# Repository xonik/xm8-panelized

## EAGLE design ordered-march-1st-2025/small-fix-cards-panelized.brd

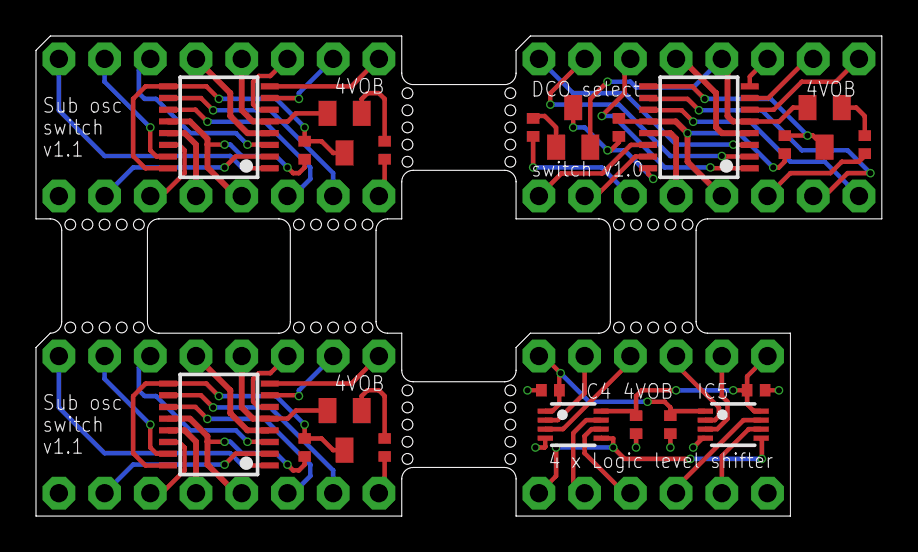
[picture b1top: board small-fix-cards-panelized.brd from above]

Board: 2 copper layers, 47.0 x 26.7 mm, 29 parts (0 on the bottom side), 66 nets.

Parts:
C1, C2, C3, C4: 1uF; C0402-J
IC1, IC2, IC3: DG412-JT; TSSOP16J
IC4, IC5: SN74LVC2T45; VSSOP8J
R1, R2, R5, R6: 10k; R0402
R3, R4, R7, R8: 470R; R0402
T1, T2, T3, T4: 2n3904; SOT23-BEC
X1, X2, X3, X4, X5, X6: ROUND-IC-PIN; MA08N-1J
X7, X8: MA06-1JN; MA06N-1J

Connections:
1_A_SUB_WAVE: IC2.1, X1.1
1_A_SUB_WAVE1: IC1.1, X3.1
1_OSC_B_OUT: IC3.3, X5.1
2_SSA1A: IC2.15, X1.2
2_SSA1A1: IC1.15, X3.2
2_WAVE_B_OUT: IC3.2, X5.2
3_A_SUB_1: IC2.3, X1.3
3_A_SUB_2: IC1.3, X3.3
3_B_MODE: IC3.1, X5.3
6_A_MODE: IC3.8, X5.6
6_A_SUB_1: IC1.6, X3.6
6_A_SUB_2: IC2.6, X1.6
7_SSQ2A: IC2.7, X1.7
7_SSQ2A1: IC1.7, X3.7
7_WAVE_A_OUT: IC3.7, X5.7
8_A_SUB_WAVE: IC2.8, X1.8
8_A_SUB_WAVE1: IC1.8, X3.8
8_OSC_A_OUT: IC3.6, X5.8
9_A_SUB_WAVE: R2.1, X2.1
9_A_SUB_WAVE1: R1.1, X4.1
9_OSC_A_OUT: IC3.11, X6.1
10_SSA2A: IC2.10, X2.2
10_SSA2A1: IC1.10, X4.2
10_WF_A_OUT: IC3.10, X6.2
11_A_MODE: R6.1, X6.3
11_A_SUB_1: IC1.11, X4.3
11_A_SUB_2: IC2.11, X2.3
11_NOT_A_MODE: IC3.9, R8.1, T4.C
14_A_SUB_1: IC2.14, X2.6
14_A_SUB_2: IC1.14, X4.6
14_B_MODE: R5.1, X6.6
14_NOT_B_MODE: IC3.16, R7.1, T3.C
15_SSQ1A: IC2.2, X2.7
15_SSQ1A1: IC1.2, X4.7
15_WF_B_OUT: IC3.15, X6.7
16_OSC_B_OUT: IC3.14, X6.8
+3V3: C1.1, C3.1, IC4.1, IC5.1, X7.1
+5V: C2.1, C4.1, IC4.8, IC5.8, X7.6
A3: IC4.2, X7.2
A4: IC4.3, X7.3
A5: IC5.2, X7.4
A6: IC5.3, X7.5
B1: IC4.7, X8.5
B2: IC4.6, X8.4
B3: IC5.7, X8.3
B4: IC5.6, X8.2
DIR: IC4.5, IC5.5, X8.6
GND: IC2.5, T2.E, X1.5
GND1: IC1.5, T1.E, X3.5
GND2: IC3.5, T3.E, T4.E, X5.5
GND3: C1.2, C2.2, C3.2, C4.2, IC4.4, IC5.4, X8.1
unnamed: R1.2, T1.B
unnamed: R2.2, T2.B
unnamed: R5.2, T3.B
unnamed: R6.2, T4.B
NOT_A_SUB_WAVE: IC2.9, IC2.16, R4.1, T2.C
NOT_A_SUB_WAVE1: IC1.9, IC1.16, R3.1, T1.C
V+: IC2.13, X2.5
V+1: IC1.13, X4.5
V+2: IC3.13, X6.5
V-: IC2.4, X1.4
V-1: IC1.4, X3.4
V-2: IC3.4, X5.4
V_L: IC2.12, R4.2, X2.4
V_L1: IC1.12, R3.2, X4.4
V_L2: IC3.12, R7.2, R8.2, X6.4

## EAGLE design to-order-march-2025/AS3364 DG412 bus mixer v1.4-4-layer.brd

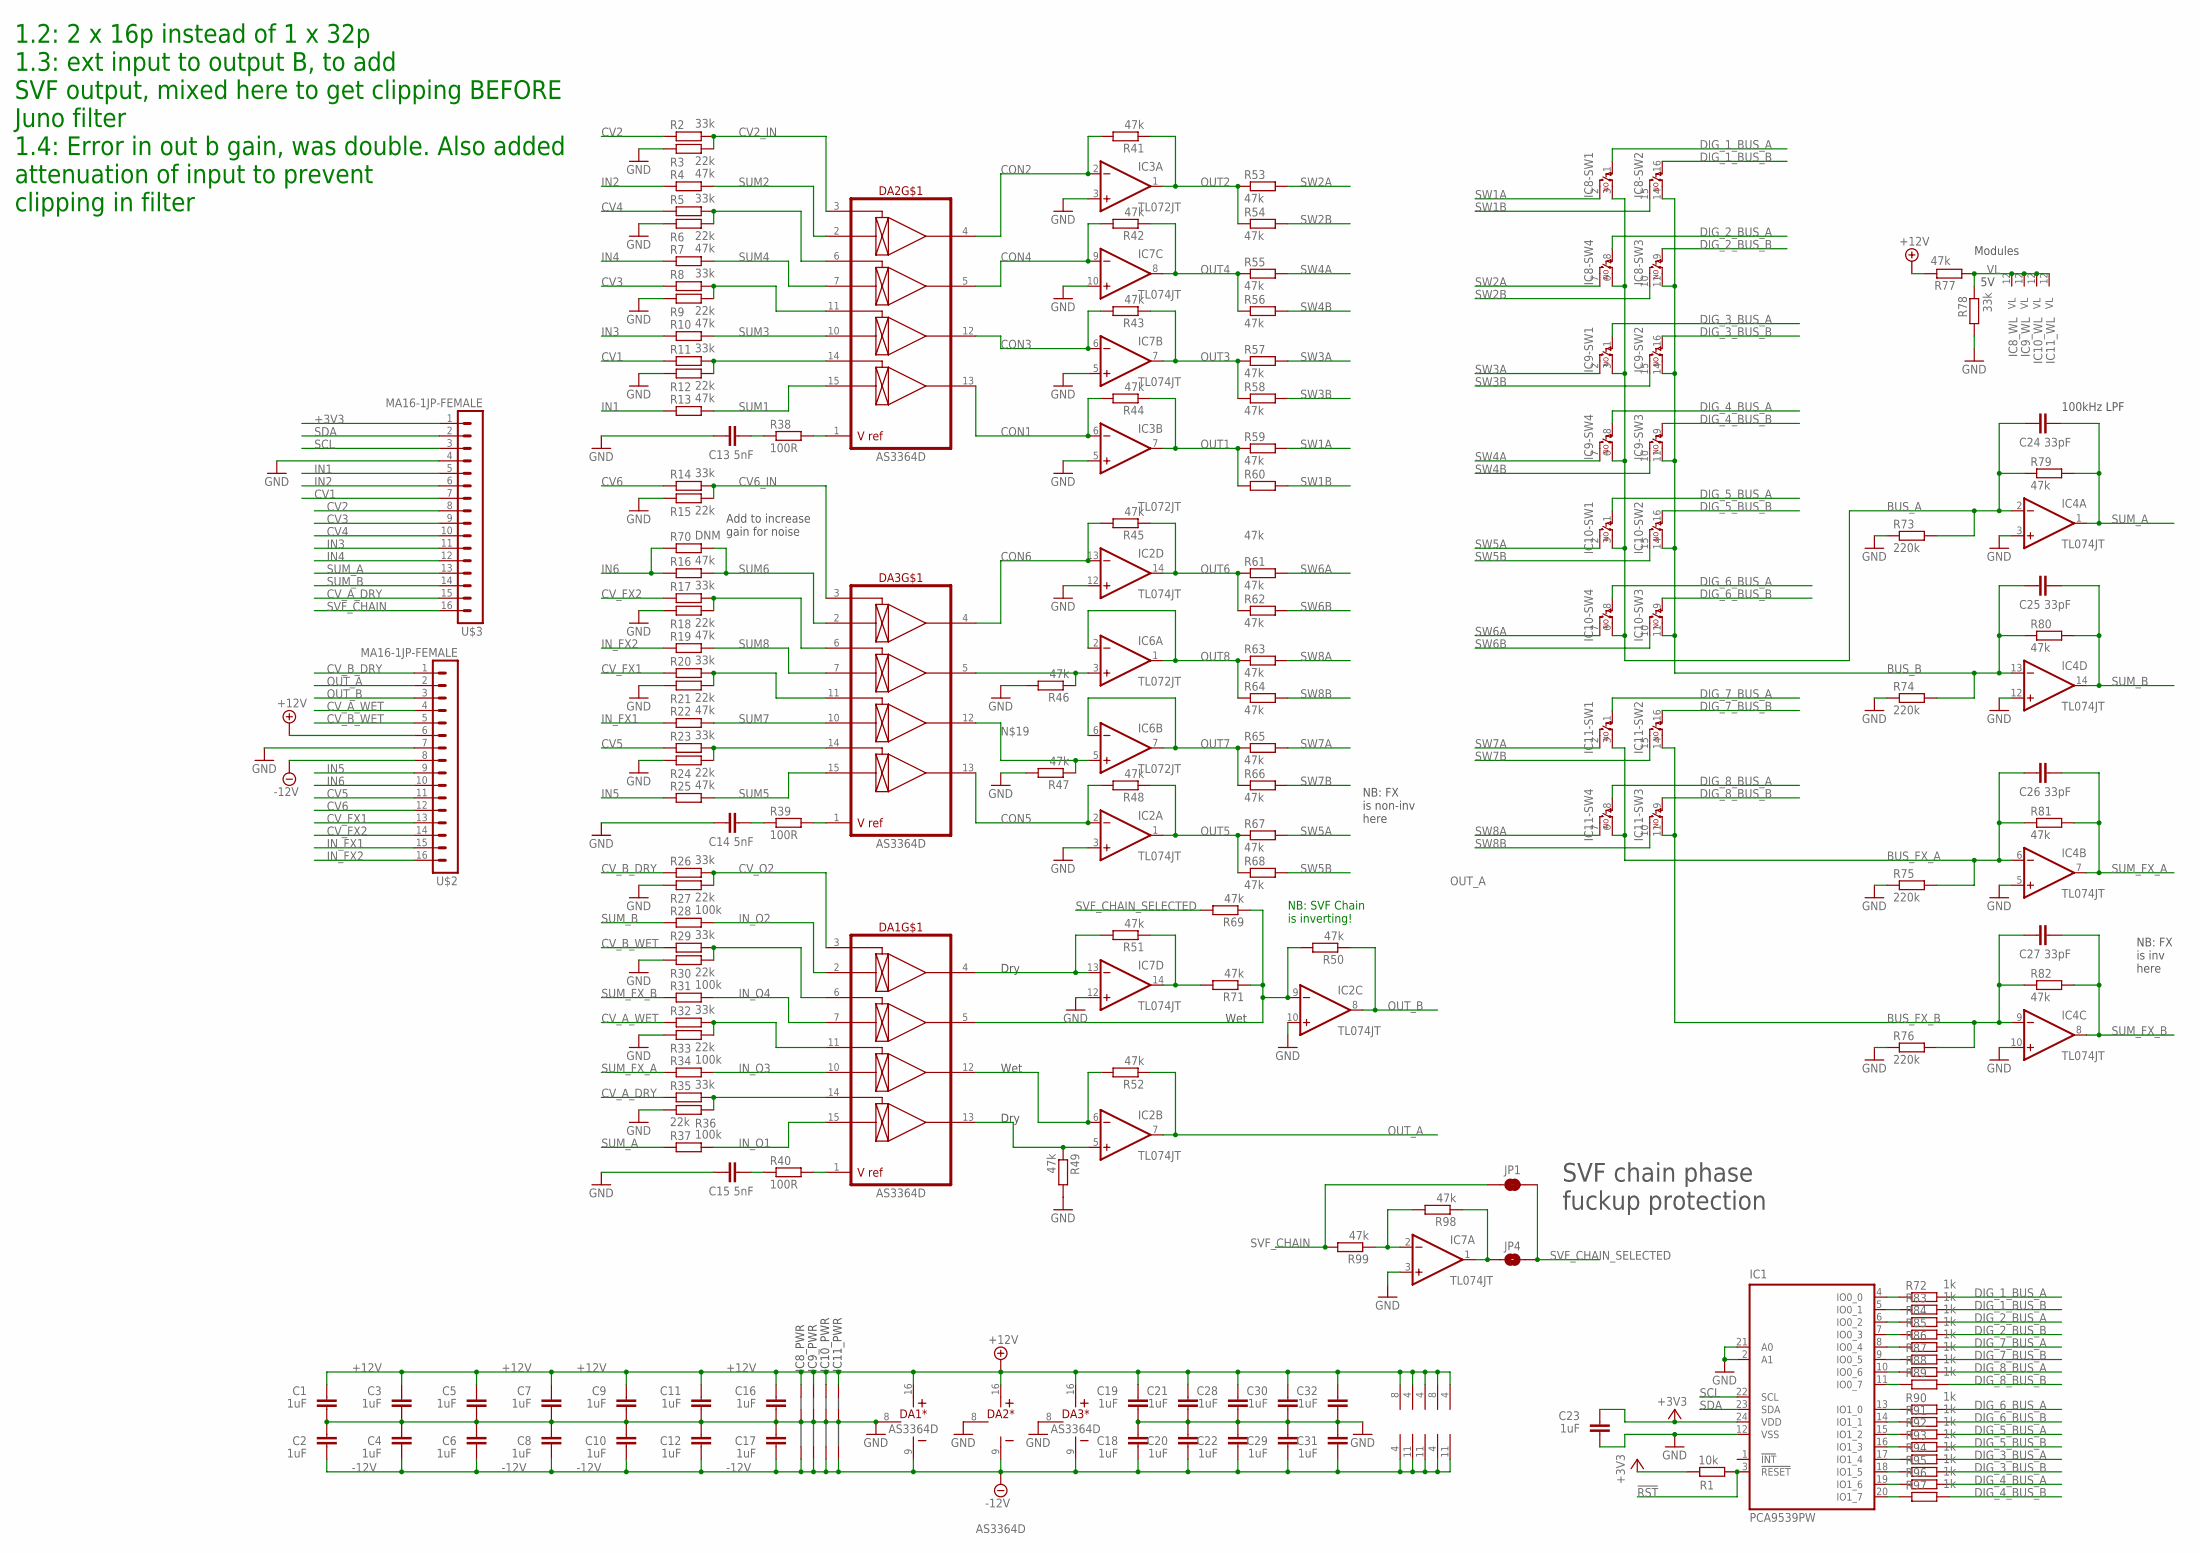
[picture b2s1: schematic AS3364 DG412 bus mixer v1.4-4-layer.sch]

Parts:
C1, C2, C3, C4, C5, C6, C7, C8, C9, C10, C11, C12, C16, C17, C18, C19, C20, C21, C22, C23, C28, C29, C30, C31, C32: 1uF; C0402-J
C13, C14, C15: 5nF; C0402-J
C24, C25, C26, C27: 33pF; C0402-J
DA1, DA2, DA3: AS3364D; DIL16J
IC1: PCA9539PW; TSSOP24J
IC2, IC4, IC7: TL074JT; TSSOP14J
IC3, IC6: TL072JT; TSSOP8J
IC8, IC9, IC10, IC11: DG412-J; DIL16J
JP1: JUMPER-SMT_2_NC_TRACE_SILK-DNM; SMT-JUMPER_2_NC_TRACE_SILK
JP4: JUMPER-SMT_2_NO_SILK-DNM; SMT-JUMPER_2_NO_SILK
R1: 10k; R0402
R2, R5, R8, R11, R14, R17, R20, R23, R26, R29, R32, R35, R78: 33k; R0402
R3, R6, R9, R12, R15, R18, R21, R24, R27, R30, R33, R36: 22k; R0402
R4, R7, R10, R13, R16, R19, R22, R25, R41, R42, R43, R44, R45, R46, R47, R48, R49, R50, R51, R52, R53, R54, R55, R56, R57, R58, R59, R60, R61, R62, R63, R64, R65, R66, R67, R68, R69, R71, R77, R79, R80, R81, R82, R98, R99: 47k; R0402
R28, R31, R34, R37: 100k; R0402
R38, R39, R40: 100R; R0402
R70: DNM; R0805
R72, R83, R84, R85, R86, R87, R88, R89, R90, R91, R92, R93, R94, R95, R96, R97: 1k; R0402
R73, R74, R75, R76: 220k; R0603
U$2, U$3: MA16-1JP-FEMALE; SIP-PIN16-1J

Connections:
!RST: IC1.3 (!RESET), R1.2
+3V3: C23.2, IC1.24 (VDD), R1.1, U$3.1
+12V: C1.2, C3.2, C5.2, C7.2, C9.2, C11.2, C16.2, C19.2, C21.2, C28.2, C30.2, C32.2, DA1.16 (V+), DA2.16 (V+), DA3.16 (V+), IC2.4 (V+), IC3.8 (V+), IC4.4 (V+), IC6.8 (V+), IC7.4 (V+), IC8.13 (+15V), IC9.13 (+15V), IC10.13 (+15V), IC11.13 (+15V), R77.1, U$2.6
-12V: C2.1, C4.1, C6.1, C8.1, C10.1, C12.1, C17.1, C18.1, C20.1, C22.1, C29.1, C31.1, DA1.9 (V-), DA2.9 (V-), DA3.9 (V-), IC2.11 (V-), IC3.4 (V-), IC4.11 (V-), IC6.4 (V-), IC7.11 (V-), IC8.4 (-15V), IC9.4 (-15V), IC10.4 (-15V), IC11.4 (-15V), U$2.8
BUS_A: C24.1, IC4.2 (-IN), IC8.3 (S), IC8.6 (S), IC9.3 (S), IC9.6 (S), IC10.3 (S), IC10.6 (S), R73.2, R79.1
BUS_B: C25.1, IC4.13 (-IN), IC8.11 (S), IC8.14 (S), IC9.11 (S), IC9.14 (S), IC10.11 (S), IC10.14 (S), R74.2, R80.1
BUS_FX_A: C26.1, IC4.6 (-IN), IC11.3 (S), IC11.6 (S), R75.2, R81.1
BUS_FX_B: C27.1, IC4.9 (-IN), IC11.11 (S), IC11.14 (S), R76.2, R82.1
CON1: DA2.13 (OUT4), IC3.6 (-IN), R44.2
CON2: DA2.4 (OUT1), IC3.2 (-IN), R41.2
CON3: DA2.12 (OUT3), IC7.6 (-IN), R43.2
CON4: DA2.5 (OUT2), IC7.9 (-IN), R42.2
CON5: DA3.13 (OUT4), IC2.2 (-IN), R48.2
CON6: DA3.4 (OUT1), IC2.13 (-IN), R45.2
CON_O1: DA1.12 (OUT3), IC2.6 (-IN), R52.2
CV1: R11.1, U$3.7
CV2: R2.1, U$3.8
CV2_IN: DA2.3 (CV1), R2.2, R3.2
CV3: R8.1, U$3.9
CV4: R5.1, U$3.10
CV5: R23.1, U$2.11
CV6: R14.1, U$2.12
CV6_IN: DA3.3 (CV1), R14.2, R15.2
CV_A_DRY: R35.1, U$3.15
CV_A_WET: R32.1, U$2.4
CV_B_DRY: R26.1, U$2.1
CV_B_WET: R29.1, U$2.5
CV_FX1: R20.1, U$2.13
CV_FX2: R17.1, U$2.14
CV_O2: DA1.3 (CV1), R26.2, R27.2
DIG_1_BUS_A: IC8.1 (C), R72.2
DIG_1_BUS_B: IC8.16 (C), R83.2
DIG_2_BUS_A: IC8.8 (C), R84.2
DIG_2_BUS_B: IC8.9 (C), R85.2
DIG_3_BUS_A: IC9.1 (C), R94.2
DIG_3_BUS_B: IC9.16 (C), R95.2
DIG_4_BUS_A: IC9.8 (C), R96.2
DIG_4_BUS_B: IC9.9 (C), R97.2
DIG_5_BUS_A: IC10.1 (C), R92.2
DIG_5_BUS_B: IC10.16 (C), R93.2
DIG_6_BUS_A: IC10.8 (C), R90.2
DIG_6_BUS_B: IC10.9 (C), R91.2
DIG_7_BUS_A: IC11.1 (C), R86.2
DIG_7_BUS_B: IC11.16 (C), R87.2
DIG_8_BUS_A: IC11.8 (C), R88.2
DIG_8_BUS_B: IC11.9 (C), R89.2
GND: C1.1, C2.2, C3.1, C4.2, C5.1, C6.2, C7.1, C8.2, C9.1, C10.2, C11.1, C12.2, C13.1, C14.1, C15.1, C16.1, C17.2, C18.2, C19.1, C20.2, C21.1, C22.2, C23.1, C28.1, C29.2, C30.1, C31.2, C32.1, DA1.8 (GND), DA2.8 (GND), DA3.8 (GND), IC1.2 (A1), IC1.12 (VSS), IC1.21 (A0), IC2.3 (+IN), IC2.10 (+IN), IC2.12 (+IN), IC3.3 (+IN), IC3.5 (+IN), IC4.3 (+IN), IC4.5 (+IN), IC4.10 (+IN), IC4.12 (+IN), IC7.3 (+IN), IC7.5 (+IN), IC7.10 (+IN), IC7.12 (+IN), IC8.5 (AGND), IC9.5 (AGND), IC10.5 (AGND), IC11.5 (AGND), R3.1, R6.1, R9.1, R12.1, R15.1, R18.1, R21.1, R24.1, R27.1, R30.1, R33.1, R36.1, R46.2, R47.2, R49.2, R73.1, R74.1, R75.1, R76.1, R78.2, U$2.7, U$3.4
IN1: R13.1, U$3.5
IN2: R4.1, U$3.6
IN3: R10.1, U$3.11
IN4: R7.1, U$3.12
IN5: R25.1, U$2.9
IN6: R16.1, R70.1, U$2.10
IN_FX1: R22.1, U$2.15
IN_FX2: R19.1, U$2.16
IN_O1: DA1.15 (IN4), R37.2
IN_O2: DA1.2 (IN1), R28.2
IN_O3: DA1.10 (IN3), R34.2
IN_O4: DA1.7 (IN2), R31.2
unnamed: DA3.1 (VREF), R39.2
unnamed: DA2.1 (VREF), R38.2
unnamed: DA3.6 (CV2), R17.2, R18.2
unnamed: DA3.5 (OUT2), IC6.3 (+IN), R46.1
unnamed: DA3.11 (CV3), R20.2, R21.2
unnamed: DA1.5 (OUT2), IC2.9 (-IN), R50.2, R69.1, R71.1
unnamed: DA3.14 (CV4), R23.2, R24.2
unnamed: C14.2, R39.1
unnamed: DA1.1 (VREF), R40.2
unnamed: DA2.6 (CV2), R5.2, R6.2
unnamed: DA1.6 (CV2), R29.2, R30.2
unnamed: DA2.11 (CV3), R8.2, R9.2
unnamed: DA1.11 (CV3), R32.2, R33.2
unnamed: C13.2, R38.1
unnamed: DA1.14 (CV4), R35.2, R36.2
unnamed: C15.2, R40.1
unnamed: DA1.4 (OUT1), IC7.13 (-IN), R51.2
unnamed: DA1.13 (OUT4), IC2.5 (+IN), R49.1
unnamed: DA3.12 (OUT3), IC6.5 (+IN), R47.1
unnamed: IC7.14 (OUT), R51.1, R71.2
unnamed: DA2.14 (CV4), R11.2, R12.2
unnamed: IC7.1 (OUT), JP4.1, R98.1
unnamed: IC1.4 (IO0_0), R72.1
unnamed: IC1.5 (IO0_1), R83.1
unnamed: IC1.6 (IO0_2), R84.1
unnamed: IC1.7 (IO0_3), R85.1
unnamed: IC1.8 (IO0_4), R86.1
unnamed: IC1.9 (IO0_5), R87.1
unnamed: IC1.10 (IO0_6), R88.1
unnamed: IC1.11 (IO0_7), R89.1
unnamed: IC1.13 (IO1_0), R90.1
unnamed: IC1.14 (IO1_1), R91.1
unnamed: IC1.15 (IO1_2), R92.1
unnamed: IC1.16 (IO1_3), R93.1
unnamed: IC1.17 (IO1_4), R94.1
unnamed: IC1.18 (IO1_5), R95.1
unnamed: IC1.19 (IO1_6), R96.1
unnamed: IC1.20 (IO1_7), R97.1
unnamed: IC7.2 (-IN), R98.2, R99.1
OUT1: IC3.7 (OUT), R44.1, R59.1, R60.1
OUT2: IC3.1 (OUT), R41.1, R53.1, R54.1
OUT3: IC7.7 (OUT), R43.1, R57.1, R58.1
OUT4: IC7.8 (OUT), R42.1, R55.1, R56.1
OUT5: IC2.1 (OUT), R48.1, R67.1, R68.1
OUT6: IC2.14 (OUT), R45.1, R61.1, R62.1
OUT7: IC6.6 (-IN), IC6.7 (OUT), R65.1, R66.1
OUT8: IC6.1 (OUT), IC6.2 (-IN), R63.1, R64.1
OUT_A: IC2.7 (OUT), R52.1, U$2.2
OUT_B: IC2.8 (OUT), R50.1, U$2.3
SCL: IC1.22 (SCL), U$3.3
SDA: IC1.23 (SDA), U$3.2
SUM1: DA2.15 (IN4), R13.2
SUM2: DA2.2 (IN1), R4.2
SUM3: DA2.10 (IN3), R10.2
SUM4: DA2.7 (IN2), R7.2
SUM5: DA3.15 (IN4), R25.2
SUM6: DA3.2 (IN1), R16.2, R70.2
SUM7: DA3.10 (IN3), R22.2
SUM8: DA3.7 (IN2), R19.2
SUM_A: C24.2, IC4.1 (OUT), R37.1, R79.2, U$3.13
SUM_B: C25.2, IC4.14 (OUT), R28.1, R80.2, U$3.14
SUM_FX_A: C26.2, IC4.7 (OUT), R34.1, R81.2
SUM_FX_B: C27.2, IC4.8 (OUT), R31.1, R82.2
SVF_CHAIN: JP1.1, R99.2, U$3.16
SVF_CHAIN_SELECTED: JP1.2, JP4.2, R69.2
SW1A: IC8.2 (D), R59.2
SW1B: IC8.15 (D), R60.2
SW2A: IC8.7 (D), R53.2
SW2B: IC8.10 (D), R54.2
SW3A: IC9.2 (D), R57.2
SW3B: IC9.15 (D), R58.2
SW4A: IC9.7 (D), R55.2
SW4B: IC9.10 (D), R56.2
SW5A: IC10.2 (D), R67.2
SW5B: IC10.15 (D), R68.2
SW6A: IC10.7 (D), R61.2
SW6B: IC10.10 (D), R62.2
SW7A: IC11.2 (D), R65.2
SW7B: IC11.15 (D), R66.2
SW8A: IC11.7 (D), R63.2
SW8B: IC11.10 (D), R64.2
VL: IC8.12 (VL), IC9.12 (VL), IC10.12 (VL), IC11.12 (VL), R77.2, R78.1

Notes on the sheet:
SVF chain phase fuckup protection
Modules
100kHz LPF
Wet
Dry
NB: FX is non-inv here
NB: FX is inv here
1.2: 2 x 16p instead of 1 x 32p 1.3: ext input to output B, to add SVF output, mixed here to get clipping BEFORE Juno filter 1.4: Error in out b gain, was double. Also added attenuation of input to prevent clipping in filter
NB: SVF Chain is inverting!
Add to increase gain for noise

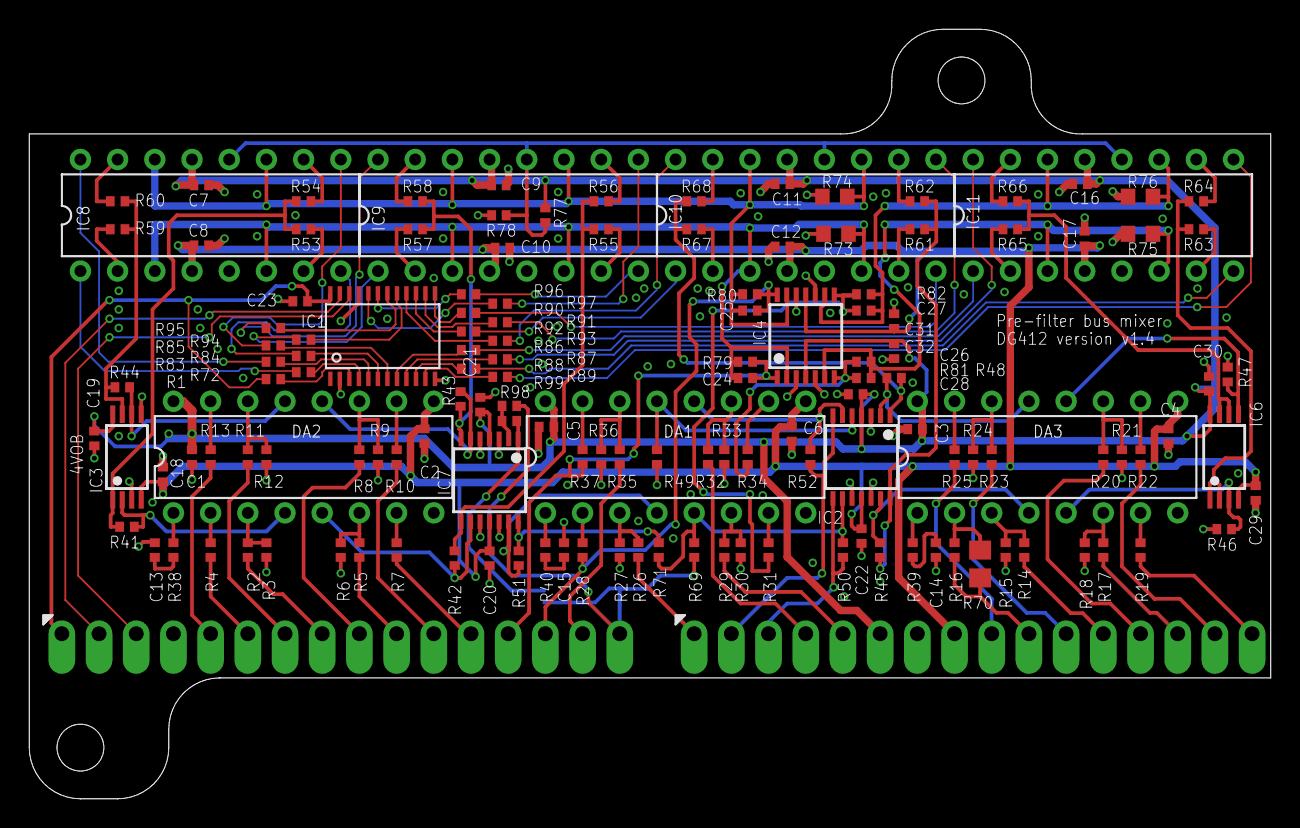
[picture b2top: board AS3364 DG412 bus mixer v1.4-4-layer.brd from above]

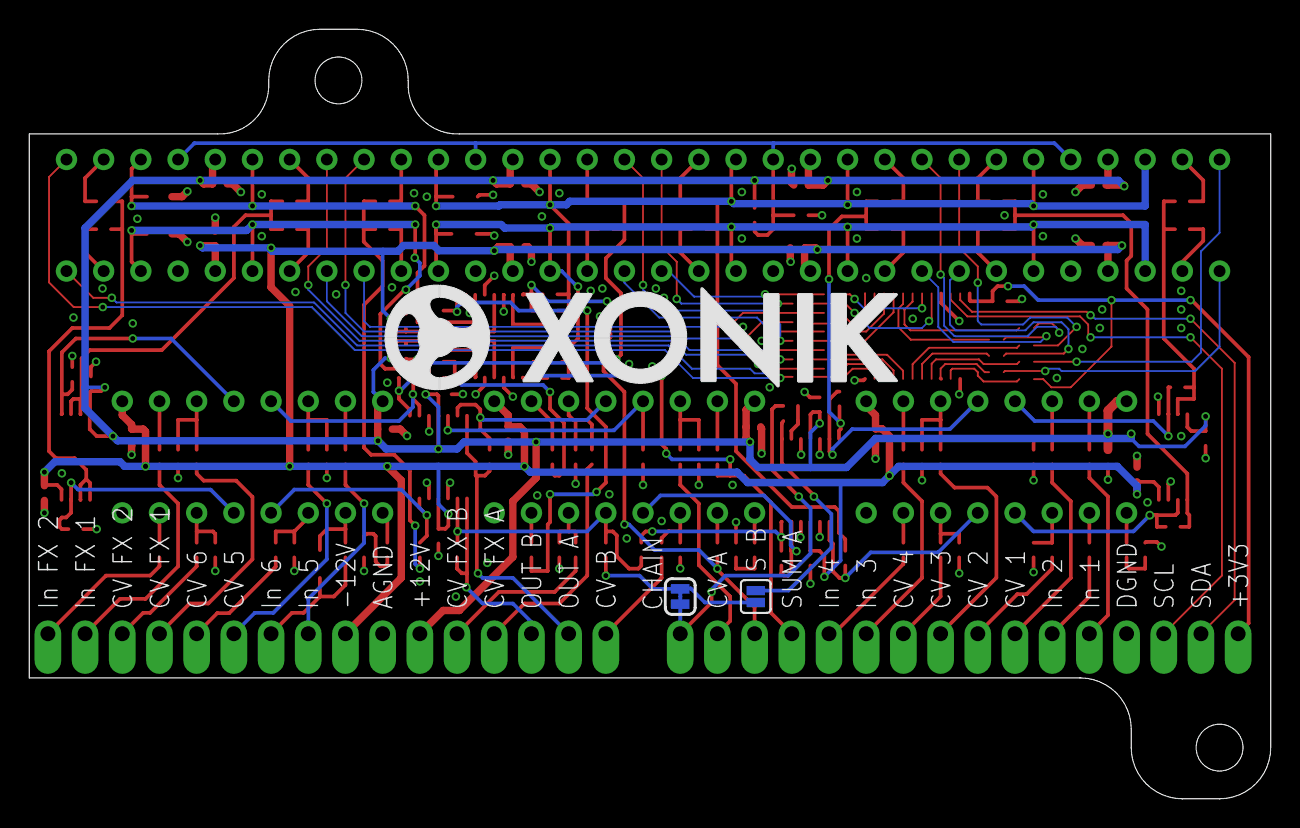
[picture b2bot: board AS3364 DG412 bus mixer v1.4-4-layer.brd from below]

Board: 4 copper layers, 84.8 x 52.5 mm, 149 parts (3 on the bottom side), 141 nets.

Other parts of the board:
U$1: XONIK_LOGO_35

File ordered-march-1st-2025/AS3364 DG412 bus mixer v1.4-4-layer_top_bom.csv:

Comment,Designator,Footprint,LCSC Part #
1k,R72 R83 R84 R85 R86 R87 R88 R89 R90 R91 R92 R93 R94 R95 R96 R97,R0402,
1uF,C1 C2 C3 C4 C5 C6 C7 C8 C9 C10 C11 C12 C16 C17 C18 C19 C20 C21 C22 C23 C28 C29 C30 C31 C32,C0402-J,
5nF,C13 C14 C15,C0402-J,
10k,R1,R0402,
22k,R3 R6 R9 R12 R15 R18 R21 R24 R27 R30 R33 R36,R0402,
33k,R2 R5 R8 R11 R14 R17 R20 R23 R26 R29 R32 R35 R78,R0402,
33pF,C24 C25 C26 C27,C0402-J,
47k,R4 R7 R10 R13 R16 R19 R22 R25 R41 R42 R43 R44 R45 R46 R47 R48 R49 R50 R51 R52 R53 R54 R55 R56 R57 R58 R59 R60 R61 R62 R63 R64 R65 R66 R67 R68 R69 R71 R77 R79 R80 R81 R82 R98 R99,R0402,
100R,R38 R39 R40,R0402,
100k,R28 R31 R34 R37,R0402,
220k,R73 R74 R75 R76,R0603,
AS3364D,DA1 DA2 DA3,DIL16J,
DG412-J,IC8 IC9 IC10 IC11,DIL16J,
DNM,R70,R0805,
JUMPER-SMT_2_NC_TRACE_SILK-DNM,JP1,SMT-JUMPER_2_NC_TRACE_SILK,
JUMPER-SMT_2_NO_SILK-DNM,JP4,SMT-JUMPER_2_NO_SILK,
MA16-1JP-FEMALE,U$2 U$3,SIP-PIN16-1J,
PCA9539PW,IC1,TSSOP24J,
TL072JT,IC3 IC6,TSSOP8J,
TL074JT,IC2 IC4 IC7,TSSOP14J,

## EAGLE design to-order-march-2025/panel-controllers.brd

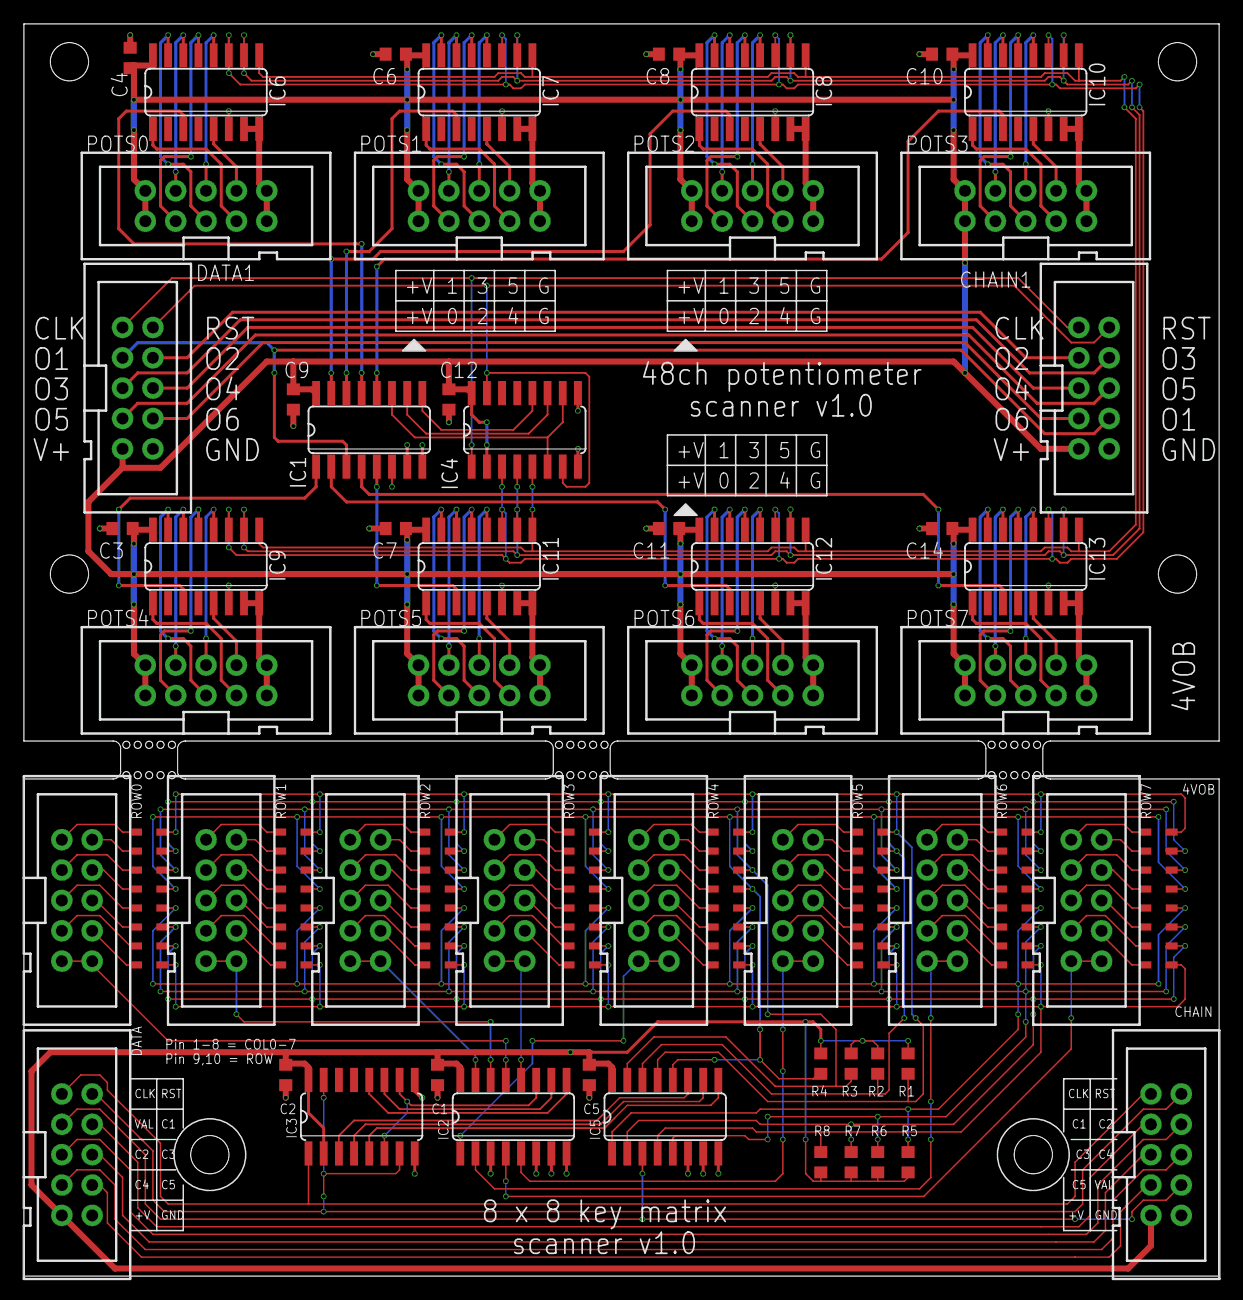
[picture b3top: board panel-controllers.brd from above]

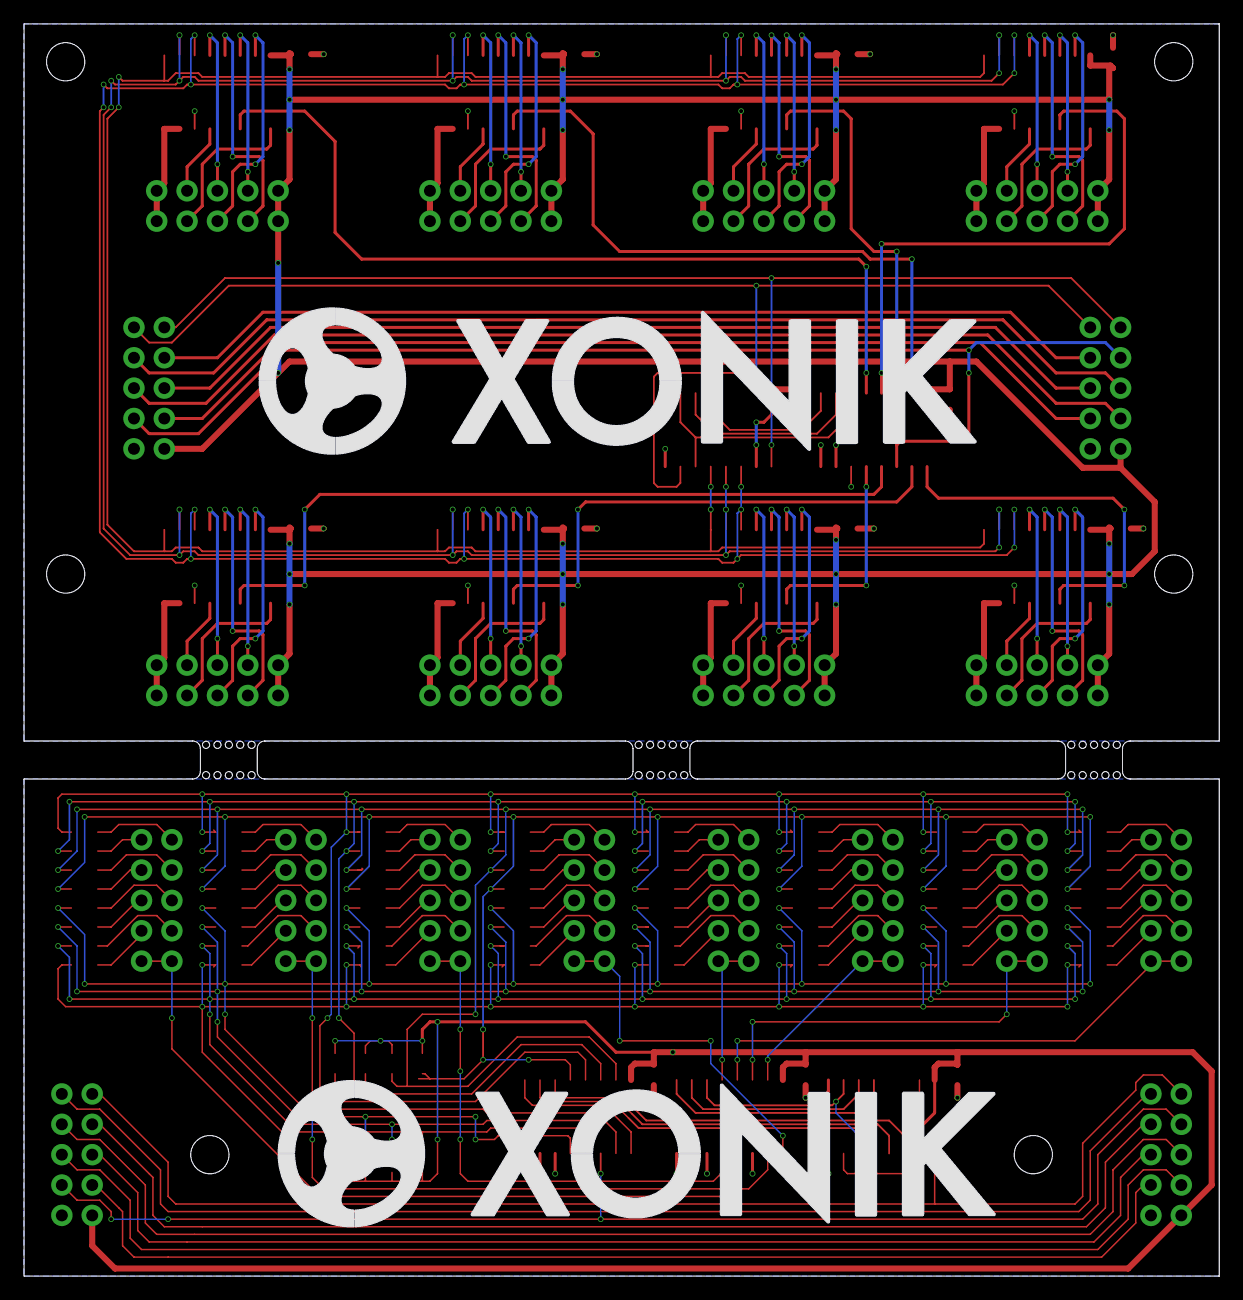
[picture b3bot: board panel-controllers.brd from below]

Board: 2 copper layers, 100.0 x 104.8 mm, 120 parts (2 on the bottom side), 168 nets.

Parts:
C1, C2, C3, C4, C5, C6, C7, C8, C9, C10, C11, C12, C14: 1uF; C0603-J
CHAIN, CHAIN1: CONN-IDC-10PS; CONN-IDC10P-S
D9, D10, D11, D12, D13, D14, D15, D16, D17, D18, D19, D20, D21, D22, D23, D24, D25, D26, D27, D28, D29, D30, D31, D32, D33, D34, D35, D36, D37, D38, D39, D40, D41, D42, D43, D44, D45, D46, D47, D48, D57, D58, D59, D60, D61, D62, D63, D64, D73, D74, D75, D76, D77, D78, D79, D80, D89, D90, D91, D92, D93, D94, D95, D96: 1N4148SOD323; SOD323J
DATA, DATA1: CONN-IDC-10PS; CONN-IDC10P-S
IC1, IC2, IC5, IC6, IC7, IC8, IC9, IC10, IC11, IC12, IC13: 4051D; SO16
IC3, IC4: 4520D; SO16
POTS0, POTS1, POTS2, POTS3, POTS4, POTS5, POTS6, POTS7: CONN-IDC-10PS; CONN-IDC10P-S
R1, R2, R3, R4, R5, R6, R7, R8: 10k; R0603
ROW0, ROW1, ROW2, ROW3, ROW4, ROW5, ROW6, ROW7: CONN-IDC-10PS; CONN-IDC10P-S
U$1, U$2: XONIK_LOGO_60

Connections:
+5V: C1.1, C2.1, C5.1, CHAIN.9, DATA.9, IC2.16, IC3.2, IC3.16, IC5.16, R1.2, R2.2, R3.2, R4.2, R5.2, R6.2, R7.2, R8.2
+5V1: C3.1, C4.1, C6.1, C7.1, C8.1, C9.1, C10.1, C11.1, C12.1, C14.1, CHAIN1.9, DATA1.9, IC1.16, IC4.2, IC4.16, IC6.16, IC7.16, IC8.16, IC9.16, IC10.16, IC11.16, IC12.16, IC13.16, POTS0.1, POTS0.2, POTS1.1, POTS1.2, POTS2.1, POTS2.2, POTS3.1, POTS3.2, POTS4.1, POTS4.2, POTS5.1, POTS5.2, POTS6.1, POTS6.2, POTS7.1, POTS7.2
BUTTON_VALUE: CHAIN.8, DATA.3, IC5.3
BUTTON_VAL_CHAIN_1: CHAIN.3, DATA.4
BUTTON_VAL_CHAIN_2: CHAIN.4, DATA.5
BUTTON_VAL_CHAIN_3: CHAIN.5, DATA.6
BUTTON_VAL_CHAIN_4: CHAIN.6, DATA.7
BUTTON_VAL_CHAIN_5: CHAIN.7, DATA.8
CLK: CHAIN.1, DATA.1, IC3.1
CLK1: CHAIN1.1, DATA1.1, IC4.1
COL0: D9.2, D17.2, D25.2, D33.2, D41.2, D57.2, D73.2, D89.2, IC5.13, R1.1
COL1: D10.2, D18.2, D26.2, D34.2, D42.2, D58.2, D74.2, D90.2, IC5.14, R2.1
COL2: D11.2, D19.2, D27.2, D35.2, D43.2, D59.2, D75.2, D91.2, IC5.15, R3.1
COL3: D12.2, D20.2, D28.2, D36.2, D44.2, D60.2, D76.2, D92.2, IC5.12, R4.1
COL4: D13.2, D21.2, D29.2, D37.2, D45.2, D61.2, D77.2, D93.2, IC5.1, R5.1
COL5: D14.2, D22.2, D30.2, D38.2, D46.2, D62.2, D78.2, D94.2, IC5.5, R6.1
COL6: D15.2, D23.2, D31.2, D39.2, D47.2, D63.2, D79.2, D95.2, IC5.2, R7.1
COL7: D16.2, D24.2, D32.2, D40.2, D48.2, D64.2, D80.2, D96.2, IC5.4, R8.1
COL_A: IC3.3, IC5.11
COL_B: IC3.4, IC5.10
COL_C: IC3.5, IC5.9
GND: C1.2, C2.2, C5.2, CHAIN.10, DATA.10, IC2.3, IC2.6, IC2.7, IC2.8, IC3.8, IC3.9, IC5.6, IC5.7, IC5.8
GND1: C3.2, C4.2, C6.2, C7.2, C8.2, C9.2, C10.2, C11.2, C12.2, C14.2, CHAIN1.10, DATA1.10, IC1.6, IC1.7, IC1.8, IC4.8, IC4.9, IC6.6, IC6.7, IC6.8, IC7.6, IC7.7, IC7.8, IC8.6, IC8.7, IC8.8, IC9.6, IC9.7, IC9.8, IC10.6, IC10.7, IC10.8, IC11.6, IC11.7, IC11.8, IC12.6, IC12.7, IC12.8, IC13.6, IC13.7, IC13.8, POTS0.9, POTS0.10, POTS1.9, POTS1.10, POTS2.9, POTS2.10, POTS3.9, POTS3.10, POTS4.9, POTS4.10, POTS5.9, POTS5.10, POTS6.9, POTS6.10, POTS7.9, POTS7.10
unnamed: D9.1, ROW0.1
unnamed: D10.1, ROW0.2
unnamed: D11.1, ROW0.3
unnamed: D12.1, ROW0.4
unnamed: D13.1, ROW0.5
unnamed: D14.1, ROW0.6
unnamed: D15.1, ROW0.7
unnamed: D16.1, ROW0.8
unnamed: D17.1, ROW2.1
unnamed: D18.1, ROW2.2
unnamed: D19.1, ROW2.3
unnamed: D20.1, ROW2.4
unnamed: D21.1, ROW2.5
unnamed: D22.1, ROW2.6
unnamed: D23.1, ROW2.7
unnamed: D24.1, ROW2.8
unnamed: D25.1, ROW1.1
unnamed: D26.1, ROW1.2
unnamed: D27.1, ROW1.3
unnamed: D28.1, ROW1.4
unnamed: D29.1, ROW1.5
unnamed: D30.1, ROW1.6
unnamed: D31.1, ROW1.7
unnamed: D32.1, ROW1.8
unnamed: D33.1, ROW4.1
unnamed: D34.1, ROW4.2
unnamed: D35.1, ROW4.3
unnamed: D36.1, ROW4.4
unnamed: D37.1, ROW4.5
unnamed: D38.1, ROW4.6
unnamed: D39.1, ROW4.7
unnamed: D40.1, ROW4.8
unnamed: D41.1, ROW3.1
unnamed: D42.1, ROW3.2
unnamed: D43.1, ROW3.3
unnamed: D44.1, ROW3.4
unnamed: D45.1, ROW3.5
unnamed: D46.1, ROW3.6
unnamed: D47.1, ROW3.7
unnamed: D48.1, ROW3.8
unnamed: D57.1, ROW5.1
unnamed: D58.1, ROW5.2
unnamed: D59.1, ROW5.3
unnamed: D60.1, ROW5.4
unnamed: D61.1, ROW5.5
unnamed: D62.1, ROW5.6
unnamed: D63.1, ROW5.7
unnamed: D64.1, ROW5.8
unnamed: D73.1, ROW6.1
unnamed: D74.1, ROW6.2
unnamed: D75.1, ROW6.3
unnamed: D76.1, ROW6.4
unnamed: D77.1, ROW6.5
unnamed: D78.1, ROW6.6
unnamed: D79.1, ROW6.7
unnamed: D80.1, ROW6.8
unnamed: D89.1, ROW7.1
unnamed: D90.1, ROW7.2
unnamed: D91.1, ROW7.3
unnamed: D92.1, ROW7.4
unnamed: D93.1, ROW7.5
unnamed: D94.1, ROW7.6
unnamed: D95.1, ROW7.7
unnamed: D96.1, ROW7.8
POT0: IC6.13, POTS0.3
POT1: IC6.14, POTS0.4
POT2: IC6.15, POTS0.5
POT3: IC6.12, POTS0.6
POT4: IC6.1, POTS0.7
POT5: IC6.5, POTS0.8
POT6: IC7.13, POTS1.3
POT7: IC7.14, POTS1.4
POT8: IC7.15, POTS1.5
POT9: IC7.12, POTS1.6
POT10: IC7.1, POTS1.7
POT11: IC7.5, POTS1.8
POT12: IC8.13, POTS2.3
POT13: IC8.14, POTS2.4
POT14: IC8.15, POTS2.5
POT15: IC8.12, POTS2.6
POT16: IC8.1, POTS2.7
POT17: IC8.5, POTS2.8
POT18: IC10.13, POTS3.3
POT19: IC10.14, POTS3.4
POT20: IC10.15, POTS3.5
POT21: IC10.12, POTS3.6
POT22: IC10.1, POTS3.7
POT23: IC10.5, POTS3.8
POT24: IC9.13, POTS4.3
POT25: IC9.14, POTS4.4
POT26: IC9.15, POTS4.5
POT27: IC9.12, POTS4.6
POT28: IC9.1, POTS4.7
POT29: IC9.5, POTS4.8
POT30: IC11.13, POTS5.3
POT31: IC11.14, POTS5.4
POT32: IC11.15, POTS5.5
POT33: IC11.12, POTS5.6
POT34: IC11.1, POTS5.7
POT35: IC11.5, POTS5.8
POT36: IC12.13, POTS6.3
POT37: IC12.14, POTS6.4
POT38: IC12.15, POTS6.5
POT39: IC12.12, POTS6.6
POT40: IC12.1, POTS6.7
POT41: IC12.5, POTS6.8
POT42: IC13.13, POTS7.3
POT43: IC13.14, POTS7.4
POT44: IC13.15, POTS7.5
POT45: IC13.12, POTS7.6
POT46: IC13.1, POTS7.7
POT47: IC13.5, POTS7.8
POT_A: IC4.3, IC6.11, IC7.11, IC8.11, IC9.11, IC10.11, IC11.11, IC12.11, IC13.11
POT_B: IC4.4, IC6.10, IC7.10, IC8.10, IC9.10, IC10.10, IC11.10, IC12.10, IC13.10
POT_C: IC4.5, IC6.9, IC7.9, IC8.9, IC9.9, IC10.9, IC11.9, IC12.9, IC13.9
POT_VALUE: CHAIN1.8, DATA1.3, IC1.3
POT_VAL_CHAIN_1: CHAIN1.3, DATA1.4
POT_VAL_CHAIN_2: CHAIN1.4, DATA1.5
POT_VAL_CHAIN_3: CHAIN1.5, DATA1.6
POT_VAL_CHAIN_4: CHAIN1.6, DATA1.7
POT_VAL_CHAIN_5: CHAIN1.7, DATA1.8
RESET: CHAIN.2, DATA.2, IC3.7, IC3.15
RESET1: CHAIN1.2, DATA1.2, IC4.7, IC4.15
ROW0: IC2.13, ROW0.9, ROW0.10
ROW1: IC2.14, ROW1.9, ROW1.10
ROW2: IC2.15, ROW2.9, ROW2.10
ROW3: IC2.12, ROW3.9, ROW3.10
ROW4: IC2.1, ROW4.9, ROW4.10
ROW5: IC2.5, ROW5.9, ROW5.10
ROW6: IC2.2, ROW6.9, ROW6.10
ROW7: IC2.4, ROW7.9, ROW7.10
ROW8: IC1.13, IC6.3
ROW9: IC1.14, IC7.3
ROW10: IC1.15, IC8.3
ROW11: IC1.12, IC10.3
ROW12: IC1.1, IC9.3
ROW13: IC1.5, IC11.3
ROW14: IC1.2, IC12.3
ROW15: IC1.4, IC13.3
ROW_A: IC2.11, IC3.6, IC3.10
ROW_A1: IC1.11, IC4.6, IC4.10
ROW_B: IC2.10, IC3.11
ROW_B1: IC1.10, IC4.11
ROW_C: IC2.9, IC3.12
ROW_C1: IC1.9, IC4.12

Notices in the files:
parts and their libraries:
SparkFun-Jumpers: Licensing: Creative Commons ShareAlike 4.0 International - https://creativecommons.org/licenses/by-sa/4.0
